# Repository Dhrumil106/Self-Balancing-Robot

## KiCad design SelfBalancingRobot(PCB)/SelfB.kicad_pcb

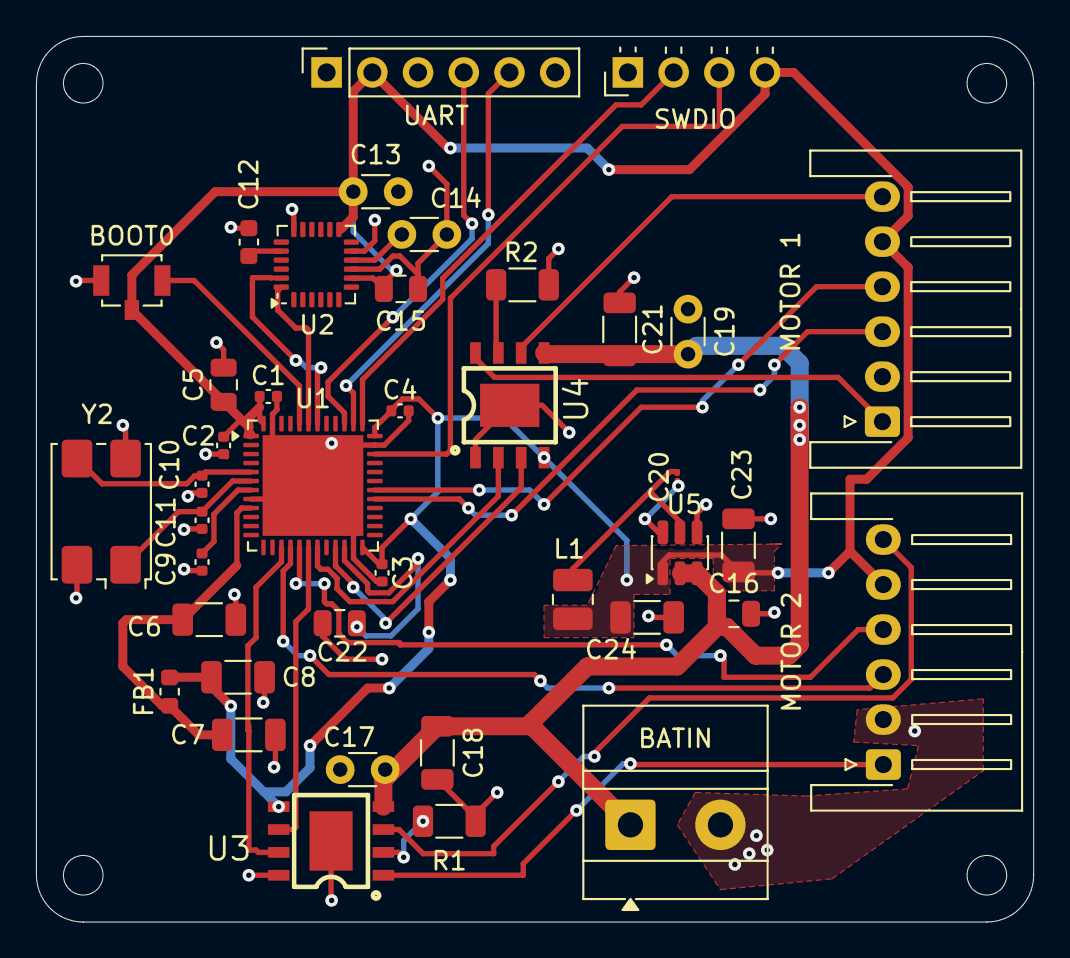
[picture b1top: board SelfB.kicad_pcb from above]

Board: 2 copper layers, 55.4 x 49.2 mm, 44 parts (0 on the bottom side), 33 nets.

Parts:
BATIN: BAT_IN; TerminalBlock_MetzConnect_Type011_RT05502HBLC_1x02_P5.00mm_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
BOOT0: SW_SPDT; SW_SPST_B3U-1100P
C1, C2, C3, C4, C9: 100n; C_0402_1005Metric
C5, C16: 10u; C_0805_2012Metric
C6: 10n; C_1206_3216Metric
C7, C8: 1u; C_1206_3216Metric
C10, C11: 27p; C_0402_1005Metric
C12: 2.2n; C_0603_1608Metric
C13, C14, C17, C19: 0.1u; C_Disc_D3.0mm_W1.6mm_P2.50mm
C15: 10n; C_0805_2012Metric
C18, C21: 47u; C_1206_3216Metric
C20: 100n; C_01005_0402Metric
C22: 4.7u; C_0805_2012Metric
C23, C24: 22u; C_1206_3216Metric
FB1: FerriteBead; L_0603_1608Metric
H1, H2, H3, H4: MountingHole; MountingHole_2.2mm_M2
L1: 6.8u; L_1008_2520Metric
MOTOR 1: Motor 2; JST_XH_S6B-XH-A-1_1x06_P2.50mm_Horizontal
MOTOR 2: Motor 1; JST_XH_S6B-XH-A-1_1x06_P2.50mm_Horizontal
R1, R2: 0.2; R_1206_3216Metric
SWDIO: Conn_01x04_Pin; PinHeader_1x04_P2.54mm_Horizontal
U1: STM32F411CEUx; QFN-48-1EP_7x7mm_P0.5mm_EP5.6x5.6mm
U2: MPU-6050; InvenSense_QFN-24_4x4mm_P0.5mm
U3, U4: AT8236-TP; AT8236
U5: AP63203WU; TSOT-23-6
UART: Conn_01x06_Pin; PinSocket_1x06_P2.54mm_Vertical
Y2: Crystal_GND24; Crystal_SMD_7050-4Pin_7.0x5.0mm

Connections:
+3.3VA: C6.1, C7.1, FB1.1, U1.9 (VDDA)
+3V3: BOOT0.3 (C), C1.1, C2.1, C3.1, C4.1, C5.1, C8.1, C13.1, C15.1, C23.2, C24.2, FB1.2, L1.2, MOTOR 1.5, MOTOR 2.5, SWDIO.4, U1.1 (VBAT), U1.24 (VDD), U1.36 (VDD), U1.48 (VDD), U2.8 (VLOGIC), U2.13 (VDD), U3.5 (VM), U4.4 (VREF), U5.1 (FB), UART.2
+15V: BATIN.1, C16.1, C17.2, C18.2, C19.2, C21.2, U3.4 (VREF), U4.5 (VM), U5.2 (EN), U5.3 (IN)
/SWCLK: SWDIO.2, U1.37 (PA14)
/SWDIO: SWDIO.3, U1.34 (PA13)
A5: U1.15 (PA5), U3.7 (ISEN)
A6: MOTOR 2.3, U1.16 (PA6)
A7: MOTOR 2.4, U1.17 (PA7)
A8: MOTOR 1.3, U1.29 (PA8)
A9: MOTOR 1.4, U1.30 (PA9)
A15: U1.38 (PA15), UART.5
B0: U1.18 (PB0), U3.6 (OUT1)
B1: U1.19 (PB1), U4.2 (IN2)
B3: U1.39 (PB3), UART.4
B6: U1.42 (PB6), U2.23 (SCL)
B7: U1.43 (PB7), U2.24 (SDA)
B10: U1.21 (PB10), U4.3 (IN1)
GND: BATIN.2, BOOT0.1 (A), C1.2, C2.2, C3.2, C4.2, C5.2, C6.2, C7.2, C8.2, C9.2, C10.1, C11.1, C12.2, C13.2, C14.2, C15.2, C16.2, C17.1, C18.1, C19.1, C21.1, C22.1, C23.1, C24.1, MOTOR 1.2, MOTOR 2.2, R1.2, R2.2, SWDIO.1, U1.8 (VSSA), U1.23 (VSS), U1.35 (VSS), U1.47 (VSS), U1.49 (VSS), U2.9 (AD0), U2.11 (FSYNC), U2.18 (GND), U3.8 (OUT2), U3.9 (EP), U4.1 (GND), U4.9 (EP), U5.4 (GND), UART.3, Y2.2 (G), Y2.4 (G)
H0: C10.2, U1.5 (PH0), Y2.3
H1: C11.2, U1.6 (PH1), Y2.1
MT1_OUT1: MOTOR 2.6, U3.3 (IN1)
MT1_OUT2: MOTOR 2.1, U3.1 (GND)
MT2_OUT1: MOTOR 1.6, U4.6 (OUT1)
MT2_OUT2: MOTOR 1.1, U4.8 (OUT2)
unnamed: BOOT0.2 (B), U1.44 (BOOT0)
unnamed: C9.1, U1.7 (NRST)
unnamed: C22.2, U1.22 (VCAP1)
unnamed: C12.1, U2.20 (CPOUT)
unnamed: C14.1, U2.10 (REGOUT)
unnamed: R1.1, U3.2 (IN2)
unnamed: R2.1, U4.7 (ISEN)
unnamed: C20.1, U5.6 (BST)
unnamed: C20.2, L1.1, U5.5 (SW)

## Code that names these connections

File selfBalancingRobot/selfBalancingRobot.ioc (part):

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Mcu.Name=STM32F411C(C-E)Ux
Mcu.Package=UFQFPN48
Mcu.UserName=STM32F411CEUx
PA0-WKUP.Signal=S_TIM2_CH1_ETR
PA1.Signal=S_TIM2_CH2
PA15.Mode=Asynchronous
PA15.Signal=USART1_TX
PA2.Signal=S_TIM2_CH3
PA3.Signal=S_TIM2_CH4
PA6.Signal=S_TIM3_CH1
PA7.Signal=S_TIM3_CH2
PA8.Signal=S_TIM1_CH1
PA9.Signal=S_TIM1_CH2
PB3.Mode=Asynchronous
PB3.Signal=USART1_RX
PB6.GPIOParameters=GPIO_Speed,GPIO_Pu
PB6.GPIO_Pu=GPIO_PULLUP
PB6.GPIO_Speed=GPIO_SPEED_FREQ_LOW
PB6.Mode=I2C
PB6.Signal=I2C1_SCL
PB7.GPIOParameters=GPIO_Speed,GPIO_Pu
PB7.GPIO_Pu=GPIO_PULLUP
PB7.GPIO_Speed=GPIO_SPEED_FREQ_LOW
PB7.Mode=I2C
PB7.Signal=I2C1_SDA
PH0\ -\ OSC_IN.Mode=HSE-External-Oscillator
PH0\ -\ OSC_IN.Signal=RCC_OSC_IN
PH1\ -\ OSC_OUT.Mode=HSE-External-Oscillator
PH1\ -\ OSC_OUT.Signal=RCC_OSC_OUT
RCC.HSE_VALUE=25000000
RCC.SYSCLKFreq_VALUE=100000000
RCC.SYSCLKSource=RCC_SYSCLKSOURCE_PLLCLK
board=custom
